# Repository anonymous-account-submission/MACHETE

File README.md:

# Motor Assisted Commutator to Harness Electronics in Tethered Experiments (MACHETE)

MACHETE is a motor assisted commutator that allows researchers to capture high-fidelity electro-optical data during tethered freely-moving behavior experiments with mice.

# Custom Arduino Printed Circuit Board Shield:
Our motor assisted commutator is driven and controlled by an Arduino Nano 3.x, integrated within a pair of custom printed circuit boards (PCBs) which allow users to interface with both data aquisition computers and existing commercial optogenetic and electrophysiological devices. 

# Commercially Available and Custom Made Parts 

<table class="table table-bordered table-hover table-condensed">
<thead>
<tr>
<th title="Field #1">Part Number</th>
<th title="Field #2">Distributor</th>
<th title="Field #3">Part Name</th>
<th title="Field #4">Distributor Part Number</th>
<th title="Field #5">Quantity Needed</th>
</tr>
</thead>
<tbody>
<tr>
<td align="right">1</td>
<td>Digikey</td>
<td>Micro USB 2.0 Connector</td>
<td>609-4613-1-ND</td>
<td>1</td>
</tr>
<tr>
<td align="right">2</td>
<td>Digikey</td>
<td>Connector Receptacle</td>
<td>WM3917CT-ND</td>
<td>1</td>
</tr>
<tr>
<td align="right">3</td>
<td>Digikey</td>
<td>Resistor 390 Ohm</td>
<td>311-390CRCT-ND</td>
<td>1</td>
</tr>
<tr>
<td align="right">4</td>
<td>Digikey</td>
<td>Toggle Switch</td>
<td>CKN1783CT-ND</td>
<td>1</td>
</tr>
<tr>
<td align="right">5</td>
<td>Digikey</td>
<td>Arduino Nano 3.x</td>
<td>1050-1001-ND</td>
<td>1</td>
</tr>
<tr>
<td align="right">6</td>
<td>Digikey</td>
<td>Mini USB 2.0 Connector</td>
<td>UE25BE5510H-ND</td>
<td>1</td>
</tr>
<tr>
<td align="right">7</td>
<td>Digikey</td>
<td>Right Angle Connector</td>
<td>WM1743-ND</td>
<td>1</td>
</tr>
<tr>
<td align="right">8</td>
<td>Digikey</td>
<td>Resistor 100k Ohm 0805</td>
<td>311-100KCRCT-ND</td>
<td>6</td>
</tr>
<tr>
<td align="right">9</td>
<td>Digikey</td>
<td>Hall Effect Sensor</td>
<td>AS5600-ASOMCT-ND</td>
<td>1</td>
</tr>
<tr>
<td align="right">10</td>
<td>Digikey</td>
<td>Capacitor 1 µF 0805</td>
<td>1276-1066-1-ND</td>
<td>1</td>
</tr>
<tr>
<td align="right">11</td>
<td>Digikey</td>
<td>Capacitor 10 µF 0805</td>
<td>445-7644-1-ND</td>
<td>1</td>
</tr>
<tr>
<td align="right">12</td>
<td>Digikey</td>
<td>Connector Receptacle</td>
<td>WM4783CT-ND</td>
<td>1</td>
</tr>
<tr>
<td align="right">13</td>
<td>Digikey</td>
<td>Resistor 10k Ohm 0805</td>
<td>RMCF0805FT10K0CT-ND</td>
<td>2</td>
</tr>
<tr>
<td align="right">14</td>
<td>Digikey</td>
<td>Motor Driver 20-QFN (3x3)</td>
<td>175-TMC6300-LA-TCT-ND</td>
<td>1</td>
</tr>
<tr>
<td align="right">15</td>
<td>Digikey</td>
<td>Resistor 120 mOhms 0805</td>
<td>RL12S.12FCT-ND</td>
<td>1</td>
</tr>
<tr>
<td align="right">16</td>
<td>Digikey</td>
<td>Capacitor 0.1 µF 0805</td>
<td>478-KGM21NR71H104KTCT-ND</td>
<td>3</td>
</tr>
<tr>
<td align="right">17</td>
<td>Digikey</td>
<td>Brushless DC Motor</td>
<td>1568-ROB-20441-ND</td>
<td>1</td>
</tr>
<tr>
<td align="right">18</td>
<td>Mouser</td>
<td>Red LED</td>
<td>696-SMLFT0805SRCTR</td>
<td>1</td>
</tr>
<tr>
<td align="right">19</td>
<td>Adafruit</td>
<td>M3 x 4mm threaded insert</td>
<td>4255</td>
<td>1 (Pack of 50)</td>
</tr>
<tr>
<td align="right">20</td>
<td>McMaster-Carr</td>
<td>M2 x 4mm threaded insert</td>
<td>94180A312</td>
<td>1 (Pack of 100)</td>
</tr>
<tr>
<td align="right">21</td>
<td>McMaster-Carr</td>
<td>Ball Bearing 6 mm shaft</td>
<td>4668K122</td>
<td>1</td>
</tr>
<tr>
<td align="right">22</td>
<td>McMaster-Carr</td>
<td>M3-0.5 x 6mm screw</td>
<td>91290A111</td>
<td>1</td>
</tr>
<tr>
<td align="right">23</td>
<td>McMaster-Carr</td>
<td>M3-0.5 x 10mm screw</td>
<td>91290A115</td>
<td>1</td>
</tr>
<tr>
<td align="right">24</td>
<td>McMaster-Carr</td>
<td>M2-0.4 x 8mm screw</td>
<td>91290A015</td>
<td>1</td>
</tr>
<tr>
<td align="right">25</td>
<td>Taidacent</td>
<td>Rotary Electrical Slip Ring</td>
<td>734831002031</td>
<td>1</td>
</tr>
<tr>
<td align="right">26</td>
<td>K&J Magnetics, Inc</td>
<td>Magnet (5 mm x 1mm)</td>
<td>D301</td>
<td>1</td>
</tr>
<tr>
<td align="right">27</td>
<td>Maxx Model</td>
<td>M1.6 x 4mm screw</td>
<td>M1640HCS</td>
<td>2</td>
</tr>
<tr>
<td align="right">28</td>
<td>Custom Parts</td>
<td>Top Case</td>
<td>3-D Printing</td>
<td>1</td>
</tr>
<tr>
<td align="right">29</td>
<td>Custom Parts</td>
<td>PCB attachment</td>
<td>3-D Printing</td>
<td>1</td>
</tr>
<tr>
<td align="right">30</td>
<td>Custom Parts</td>
<td>Static PCB</td>
<td>PCB Manufacturing (JLC PCB)</td>
<td>1</td>
</tr>
<tr>
<td align="right">31</td>
<td>Custom Parts</td>
<td>Dynamic PCB</td>
<td>PCB Manufacturing (JLC PCB)</td>
<td>1</td>
</tr>
<tr>
<td align="right">32</td>
<td>Custom Parts</td>
<td>Small Gear</td>
<td>3-D Printing</td>
<td>1</td>
</tr>
<tr>
<td align="right">33</td>
<td>Custom Parts</td>
<td>Shield</td>
<td>3-D Printing</td>
<td>1</td>
</tr>
<tr>
<td align="right">34</td>
<td>Custom Parts</td>
<td>Cable Holder</td>
<td>3-D Printing</td>
<td>1</td>
</tr>
<tr>
<td align="right">35</td>
<td>Custom Parts</td>
<td>Outer Gear</td>
<td>3-D Printing</td>
<td>1</td>
</tr>
</tbody>
</table>

This [document](https://github.com/anonymous-account-submission/MACHETE/blob/bac1c05d11be4005d82bf26546d7f61cbe5a9f60/3-MACHETE-Custom-Parts-Table.pdf) outlines the design of each of the custom pieces and the file types found within this repository that can be used to replicate the system. The following [spreadsheet](https://github.com/anonymous-account-submission/MACHETE/blob/89ad60d1f6e04f39b38d436aee46013fde03fa46/2-MACHETE-Bill-of-Materials-and-Assembly-Spreadsheet.xlsx) outlines the total cost of the motor assisted commutator.  

**Here is a list of the manufacturers we purchased materials from:** 
- Digikey
- Mouser
- Adafruit 
- McMaster-Carr
- Taidacent
- K&J Magnetics, Inc
- Maxx Model

# Step-by-Step Building Guide

This following [guide](https://github.com/anonymous-account-submission/MACHETE/blob/89ad60d1f6e04f39b38d436aee46013fde03fa46/4-MACHETE-Step-by-Step-Guide.pdf) provides a step-by-step walkthrough for building and testing each component of our motor assisted commutator. This document includes diagrams and explanations for assembling each component. 

# Software Installation Guide and Dependencies

Following this installation guide will ensure that your MACHETE system will be able to run the required Arduino IDE sketches to function. 

**Required Software and Applications**:
- [Arduino IDE](https://www.arduino.cc/en/software)
- [BORIS](https://github.com/olivierfriard/BORIS)
  
# Contact

Further information and requests for resources should be directed to and will be fulfilled by the lead author, [Lead Author Name and Email]. Example commutator data is available upon request to the corresponding author, [Corresponding Author Name and Email].

# Citation 

If you replicate this system in your own labs or use parts of our designs and code, we kindly ask that you please cite this [page](https://github.com/anonymous-account-submission/MACHETE) [1].

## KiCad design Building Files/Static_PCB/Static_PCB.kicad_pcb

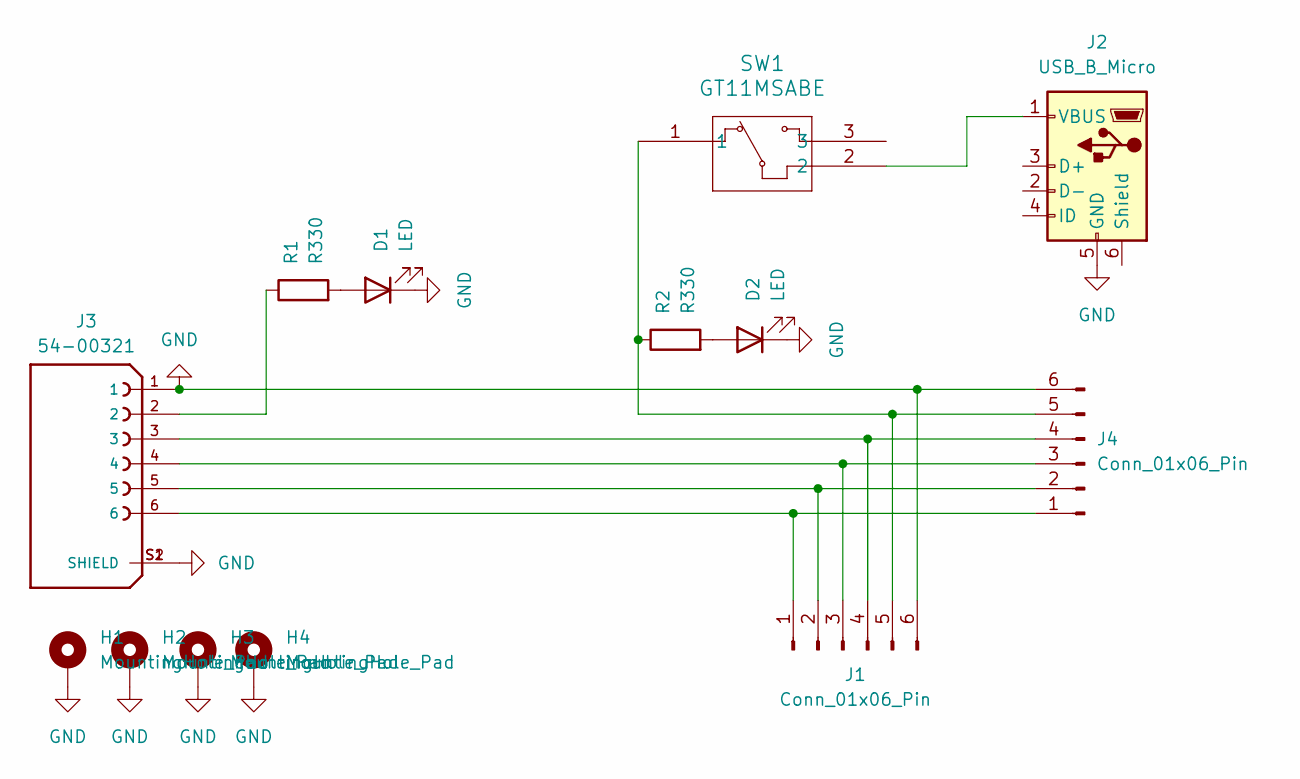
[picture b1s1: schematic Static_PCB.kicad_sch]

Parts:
D1, D2: LED; LED_0805_2012Metric
H1, H2, H3, H4: MountingHole_Pad; MountingHole_3.2mm_M3_ISO14580_Pad
J1: Conn_01x06_Pin; Molex_CLIK-Mate_502386-0670_1x06-1MP_P1.25mm_Horizontal
J2: USB_B_Micro; USB_Micro-B_Amphenol_10118194_Horizontal
J3: 54-00321; TENSILITY_54-00321; PARTREV A
J4: Conn_01x06_Pin; SolderWire-1sqmm_1x06_P5.4mm_D1.4mm_OD2.7mm
R1, R2: R330; R_0805_2012Metric
SW1: GT11MSABE; GT11MSABE_CNK

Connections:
GND: D1.1 (K), D2.1 (K), H1.1, H2.1, H3.1, H4.1, J1.6, J2.5 (GND), J3.1, J3.S1 (SHIELD), J3.S2 (SHIELD), J4.6
unnamed: D1.2 (A), R1.2
unnamed: D2.2 (A), R2.2
unnamed: J1.1, J3.6, J4.1
unnamed: J1.2, J3.5, J4.2
unnamed: J1.3, J3.4, J4.3
unnamed: J1.4, J3.3, J4.4
unnamed: J1.5, J4.5, R2.1, SW1.1
unnamed: J2.1 (VBUS), SW1.2
unnamed: J3.2, R1.1

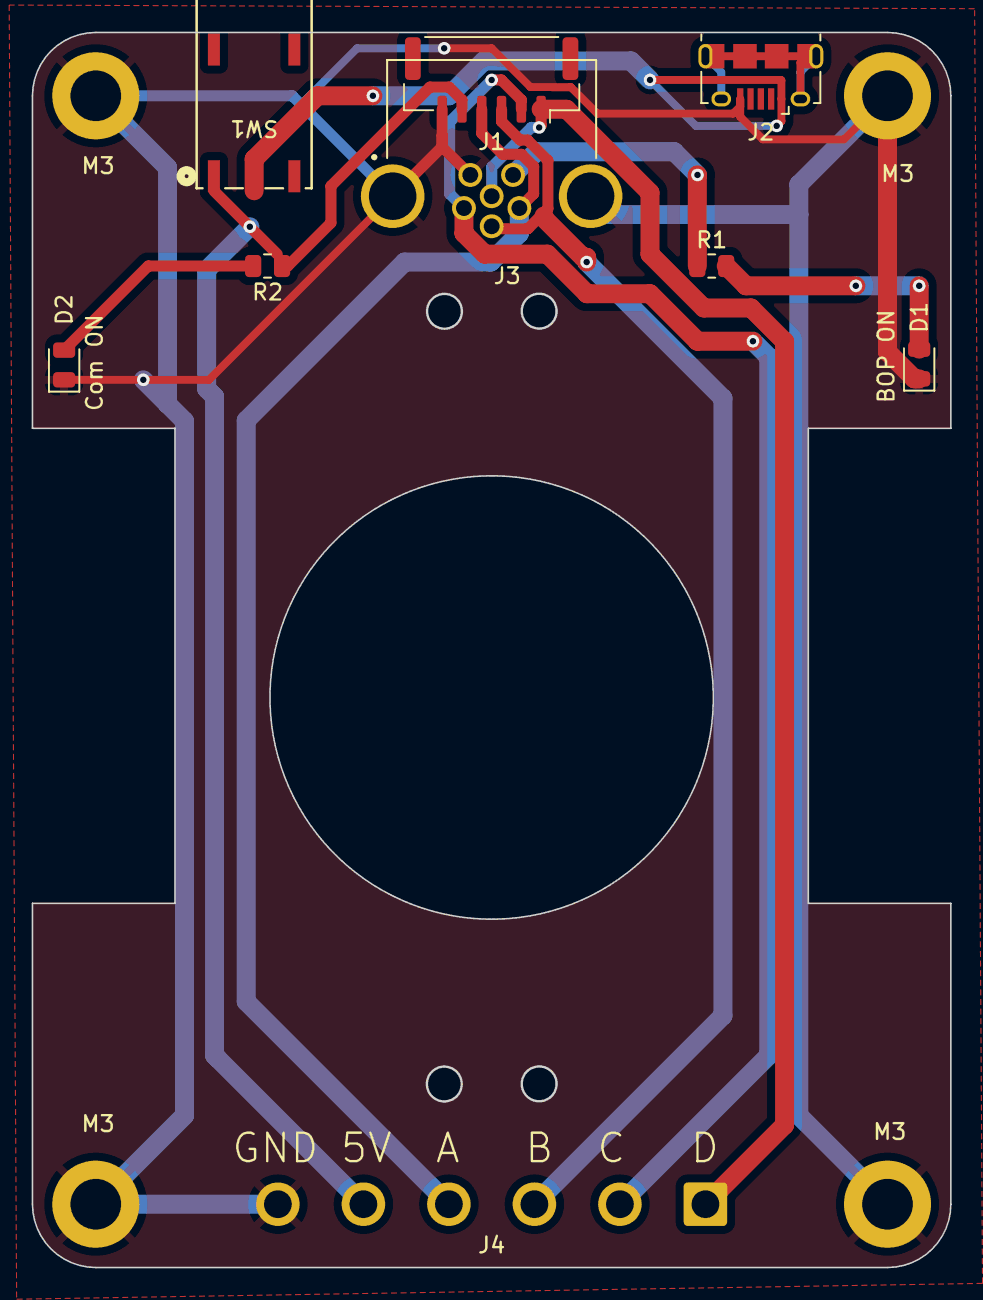
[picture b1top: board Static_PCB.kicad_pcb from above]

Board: 2 copper layers, 58.0 x 78.0 mm, 13 parts (0 on the bottom side), 10 nets.

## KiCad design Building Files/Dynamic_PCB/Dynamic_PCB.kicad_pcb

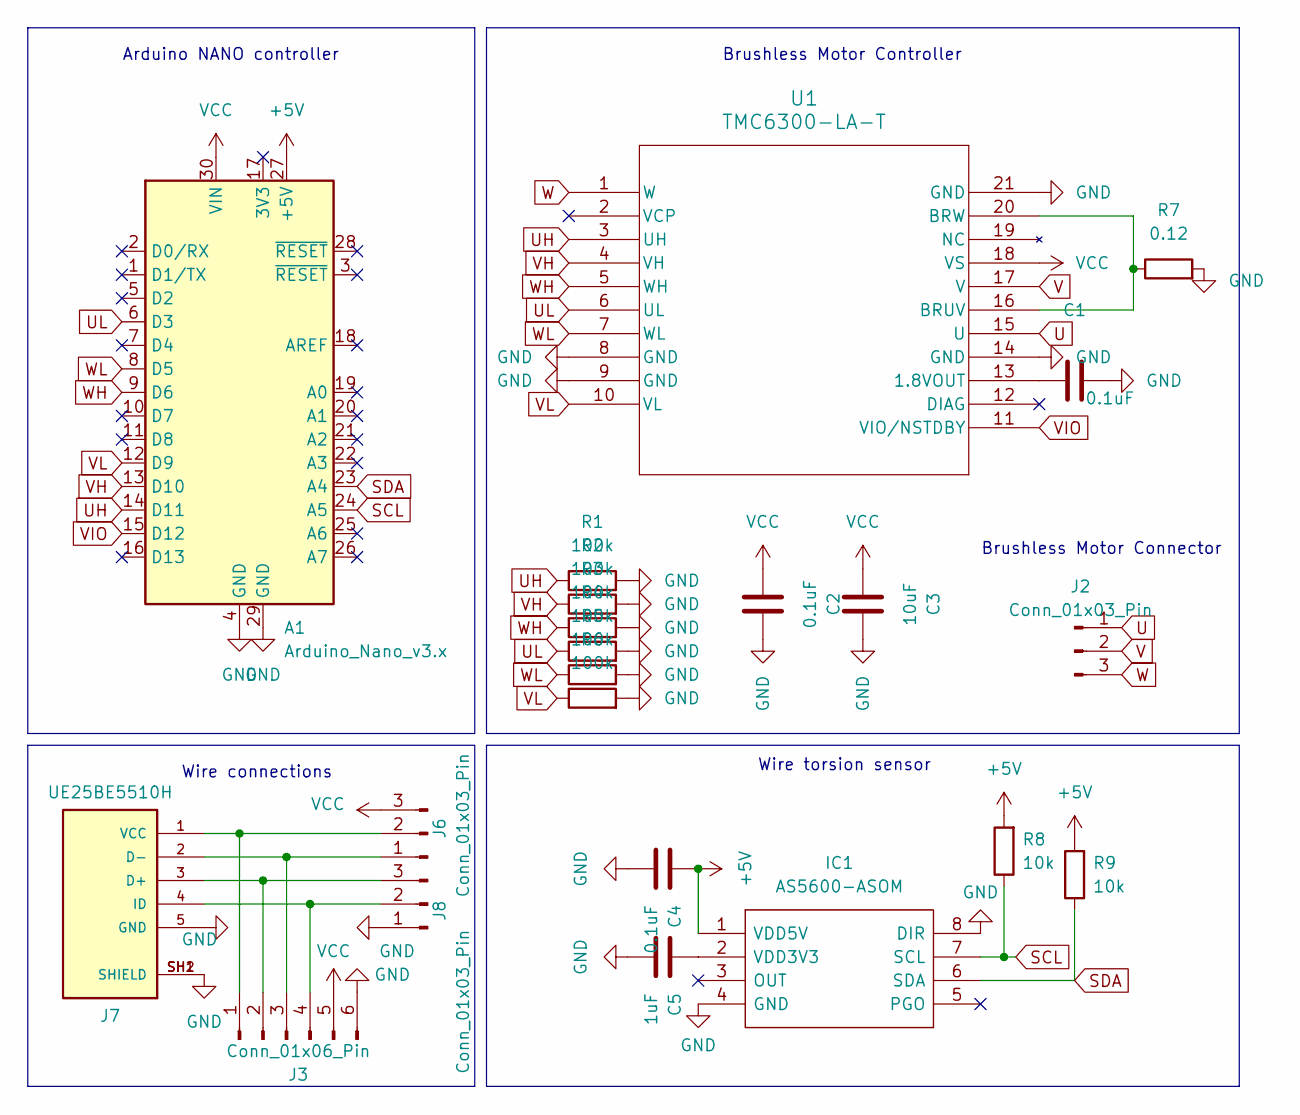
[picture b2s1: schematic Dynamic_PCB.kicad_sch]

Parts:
A1: Arduino_Nano_v3.x; Arduino_Nano_pads
C1, C2, C4: 0.1uF; C_0805_2012Metric
C3: 10uF; C_0805_2012Metric
C5: 1uF; C_0805_2012Metric
IC1: AS5600-ASOM; SOIC127P600X175-8N; Mouser Part Number 985-AS5600-ASOM
J2: Conn_01x03_Pin; PinSocket_1x03_P1.27mm_Vertical
J3: Conn_01x06_Pin; Molex_CLIK-Mate_502382-0670_1x06-1MP_P1.25mm_Vertical
J6, J8: Conn_01x03_Pin; SolderWire-1sqmm_1x03_P5.4mm_D1.4mm_OD2.7mm
J7: UE25BE5510H; AMPHENOL_UE25BE5510H; PARTREV C
R1, R2, R3, R4, R5, R6: 100k; R_0805_2012Metric
R7: 0.12; R_0805_2012Metric
R8, R9: 10k; R_0805_2012Metric
U1: TMC6300-LA-T; 21-100586_K2033&plus_1C_ADI

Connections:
+5V: A1.27 (+5V), C4.1, IC1.1 (VDD5V), R8.2, R9.2
GND: A1.4 (GND), A1.29 (GND), C1.2, C2.2, C3.2, C4.2, C5.2, IC1.4 (GND), IC1.8 (DIR), J3.6, J3.MP, J7.5 (GND), J7.SH1 (SHIELD), J7.SH2 (SHIELD), J8.1, R1.2, R2.2, R3.2, R4.2, R5.2, R6.2, R7.2, U1.8 (GND), U1.9 (GND), U1.14 (GND), U1.21 (GND)
unnamed: C5.1, IC1.2 (VDD3V3)
unnamed: J3.1, J6.2, J7.1 (VCC)
unnamed: J3.2, J7.3 (D+), J8.3
unnamed: J3.3, J6.1, J7.2 (D-)
unnamed: J3.4, J7.4 (ID), J8.2
unnamed: C1.1, U1.13 (1.8VOUT)
unnamed: R7.1, U1.16 (BRUV), U1.20 (BRW)
SCL: A1.24 (A5), IC1.7 (SCL), R8.1
SDA: A1.23 (A4), IC1.6 (SDA), R9.1
U: J2.1, U1.15 (U)
UH: A1.14 (D11), R1.1, U1.3 (UH)
UL: A1.6 (D3), R4.1, U1.6 (UL)
V: J2.2, U1.17 (V)
VCC: A1.30 (VIN), C2.1, C3.1, J3.5, J6.3, U1.18 (VS)
VH: A1.13 (D10), R2.1, U1.4 (VH)
VIO: A1.15 (D12), U1.11 (VIO/NSTDBY)
VL: A1.12 (D9), R6.1, U1.10 (VL)
W: J2.3, U1.1 (W)
WH: A1.9 (D6), R3.1, U1.5 (WH)
WL: A1.8 (D5), R5.1, U1.7 (WL)

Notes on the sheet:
Arduino NANO controller
Wire connections
Brushless Motor Controller
Wire torsion sensor
Brushless Motor Connector

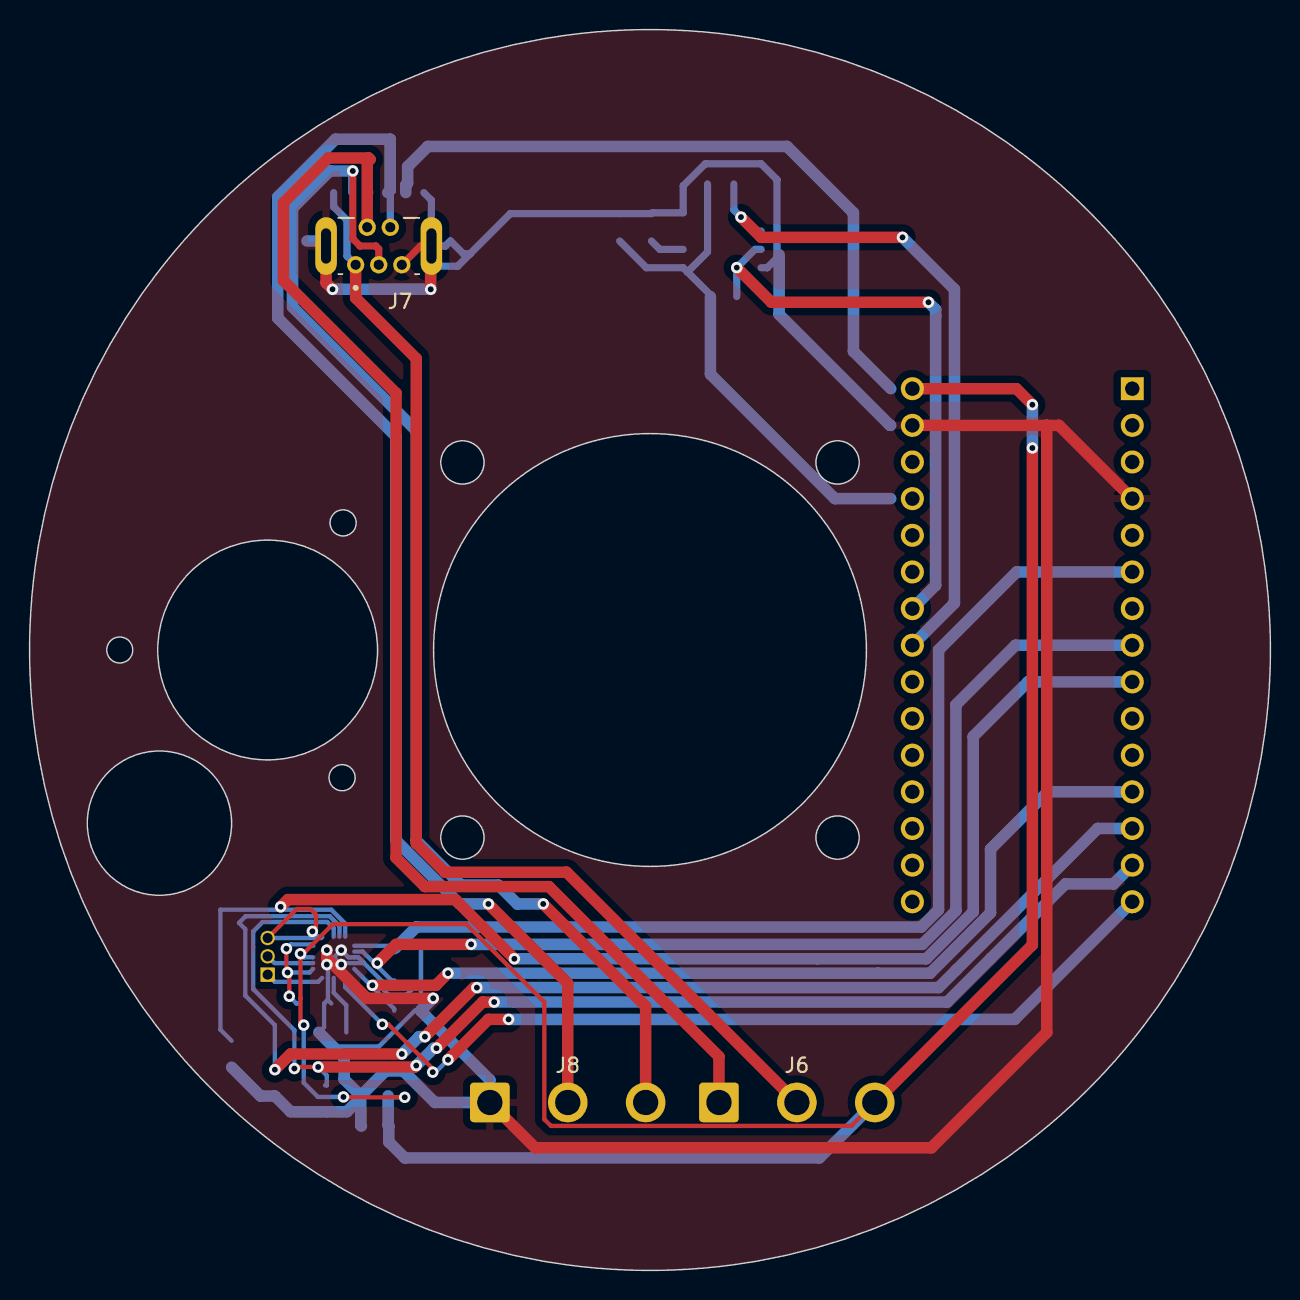
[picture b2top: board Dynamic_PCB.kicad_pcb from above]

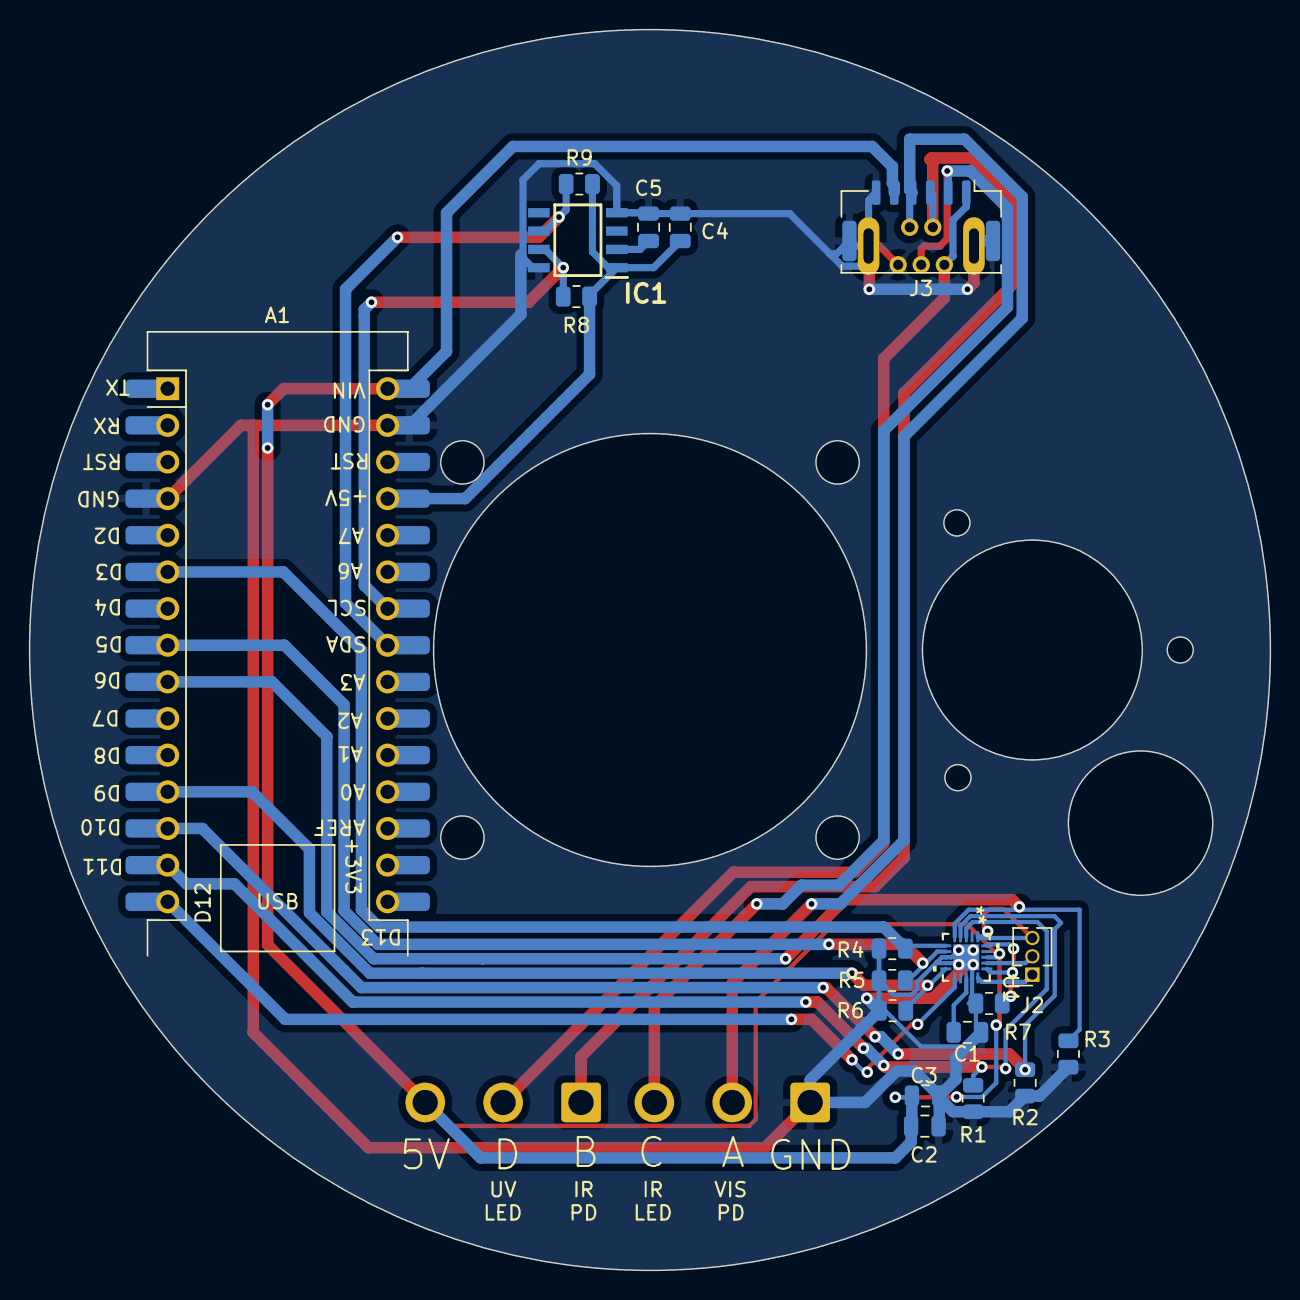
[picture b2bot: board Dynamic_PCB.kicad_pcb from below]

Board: 2 copper layers, 86.0 x 86.0 mm, 22 parts (19 on the bottom side), 22 nets.

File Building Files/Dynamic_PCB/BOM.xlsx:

Comment | Designator | Footprint | JLCPCB Part #（optional）
Conn_01x03_Pin | J2 | PinSocket_1x03_P1.27mm_Vertical
UE25BE5510H | J7 | AMPHENOL_UE25BE5510H
Conn_01x03_Pin | J8,J6 | SolderWire-1sqmm_1x03_P5.4mm_D1.4mm_OD2.7mm
100k | R1,R6,R2,R3,R4,R5 | R_0805_2012Metric
Arduino_Nano_v3.x | A1 | Arduino_Nano_pads
AS5600-ASOM | IC1 | SOIC127P600X175-8N
1uF | C5 | C_0805_2012Metric
10uF | C3 | C_0805_2012Metric
Conn_01x06_Pin | J3 | Molex_CLIK-Mate_502382-0670_1x06-1MP_P1.25mm_Vertical
10k | R9,R8 | R_0805_2012Metric
TMC6300-LA-T | U1 | 21-100586_K2033&plus_1C_ADI
0.12 | R7 | R_0805_2012Metric
0.1uF | C2,C4,C1 | C_0805_2012Metric

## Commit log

2024-12-18 Create A
